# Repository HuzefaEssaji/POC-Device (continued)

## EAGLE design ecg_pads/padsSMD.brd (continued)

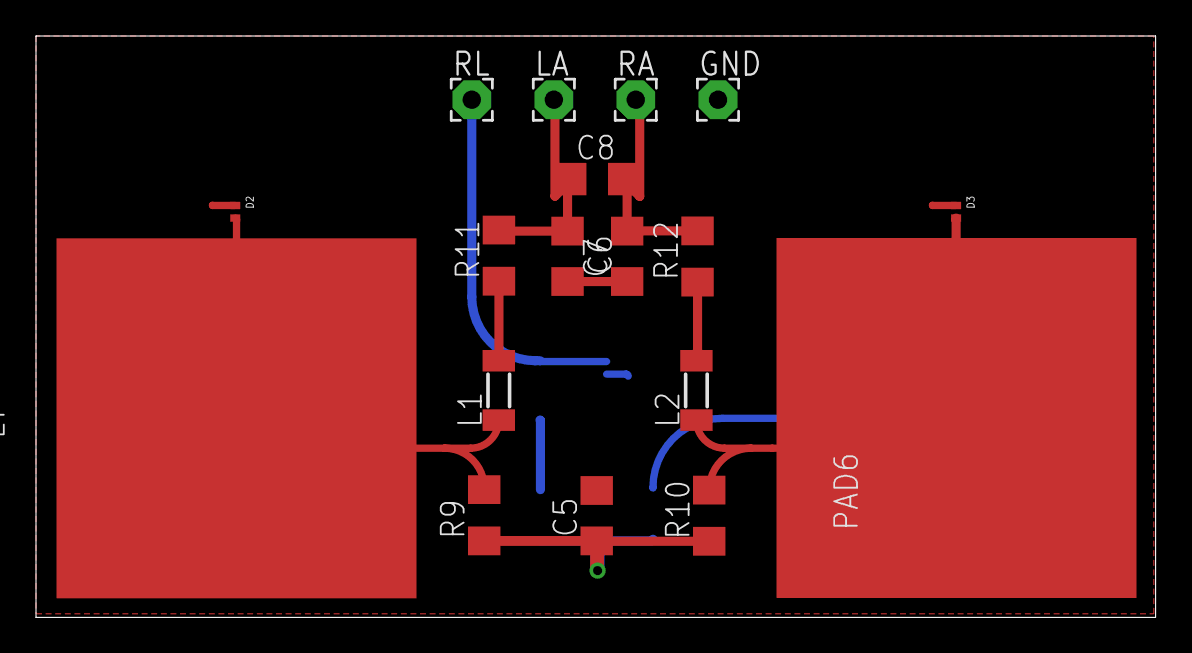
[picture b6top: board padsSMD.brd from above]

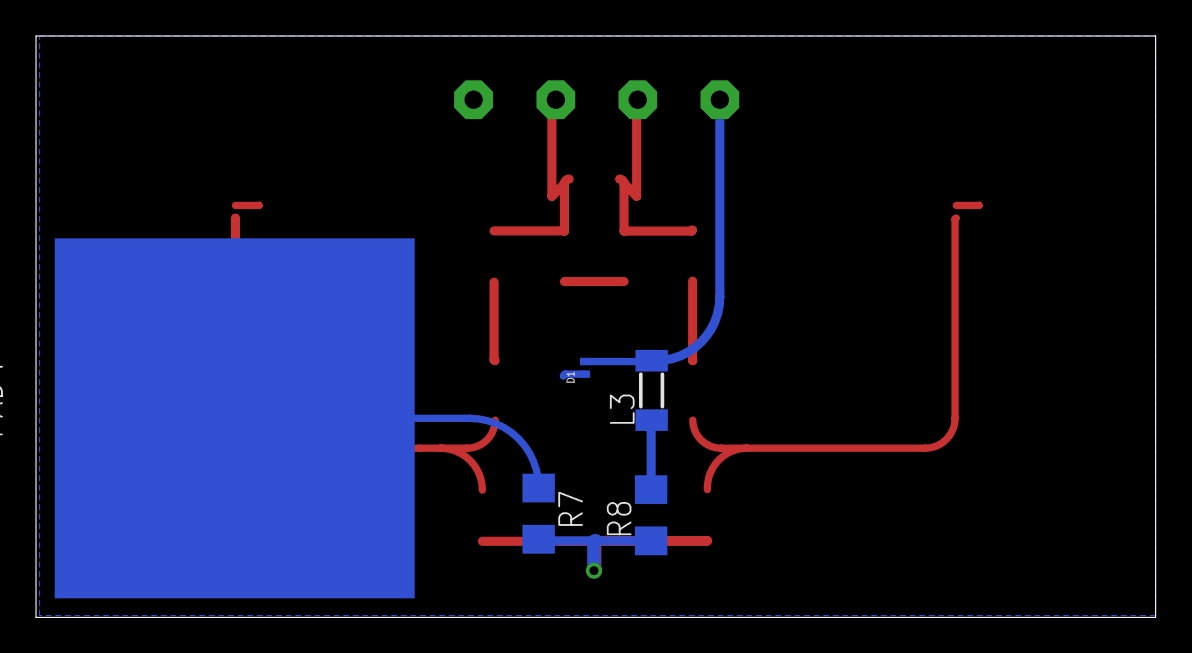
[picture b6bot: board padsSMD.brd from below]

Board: 2 copper layers, 62.2 x 32.3 mm, 23 parts (5 on the bottom side), 12 nets.

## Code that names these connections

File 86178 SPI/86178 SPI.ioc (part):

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Mcu.Name=STM32F303R(D-E)Tx
Mcu.Package=LQFP64
Mcu.UserName=STM32F303RETx
PA13.GPIOParameters=GPIO_Label
PA13.GPIO_Label=TMS
PA13.Mode=Serial_Wire
PA13.Signal=SYS_JTMS-SWDIO
PA14.GPIOParameters=GPIO_Label
PA14.GPIO_Label=TCK
PA14.Mode=Serial_Wire
PA14.Signal=SYS_JTCK-SWCLK
PA2.GPIOParameters=GPIO_Speed,GPIO_PuPd,GPIO_Label,GPIO_Mode
PA2.GPIO_Label=USART_TX
PA2.GPIO_Mode=GPIO_MODE_AF_PP
PA2.GPIO_PuPd=GPIO_NOPULL
PA2.GPIO_Speed=GPIO_SPEED_FREQ_LOW
PA2.Mode=Asynchronous
PA2.Signal=USART2_TX
PA3.GPIOParameters=GPIO_Speed,GPIO_PuPd,GPIO_Label,GPIO_Mode
PA3.GPIO_Label=USART_RX
PA3.GPIO_Mode=GPIO_MODE_AF_PP
PA3.GPIO_PuPd=GPIO_NOPULL
PA3.GPIO_Speed=GPIO_SPEED_FREQ_LOW
PA3.Mode=Asynchronous
PA3.Signal=USART2_RX
PA5.GPIOParameters=GPIO_Speed,GPIO_PuPd,GPIO_Label,GPIO_Mode
PA5.GPIO_Label=LD2 [Green Led]
PA5.GPIO_Mode=GPIO_MODE_OUTPUT_PP
PA5.GPIO_PuPd=GPIO_NOPULL
PA5.GPIO_Speed=GPIO_SPEED_FREQ_LOW
PA5.Signal=GPIO_Output
PB13.Mode=Full_Duplex_Master
PB13.Signal=SPI2_SCK
PB14.Mode=Full_Duplex_Master
PB14.Signal=SPI2_MISO
PB15.Mode=Full_Duplex_Master
PB15.Signal=SPI2_MOSI
PB3.GPIOParameters=GPIO_Label
PB3.GPIO_Label=SWO
PB3.Signal=SYS_JTDO-TRACESWO
PC13.GPIOParameters=GPIO_Label,GPIO_ModeDefaultEXTI
PC13.GPIO_Label=B1 [Blue PushButton]
PC13.GPIO_ModeDefaultEXTI=GPIO_MODE_IT_FALLING
PC13.Signal=GPXTI13
PC14-OSC32_IN.Mode=LSE-External-Oscillator
PC14-OSC32_IN.Signal=RCC_OSC32_IN
PC15-OSC32_OUT.Mode=LSE-External-Oscillator
PC15-OSC32_OUT.Signal=RCC_OSC32_OUT
PC3.Signal=GPIO_Output
PF0-OSC_IN.Mode=HSE-External-Clock-Source
PF0-OSC_IN.Signal=RCC_OSC_IN
PF1-OSC_OUT.Signal=RCC_OSC_OUT
RCC.HSE_VALUE=8000000
RCC.SYSCLKFreq_VALUE=16000000
RCC.SYSCLKSourceVirtual=RCC_SYSCLKSOURCE_PLLCLK
board=NUCLEO-F303RE
boardIOC=true

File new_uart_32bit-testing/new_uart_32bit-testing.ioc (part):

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Mcu.Name=STM32F303R(D-E)Tx
Mcu.Package=LQFP64
Mcu.UserName=STM32F303RETx
PA13.GPIOParameters=GPIO_Label
PA13.GPIO_Label=TMS
PA13.Mode=Serial_Wire
PA13.Signal=SYS_JTMS-SWDIO
PA14.GPIOParameters=GPIO_Label
PA14.GPIO_Label=TCK
PA14.Mode=Serial_Wire
PA14.Signal=SYS_JTCK-SWCLK
PA2.GPIOParameters=GPIO_Speed,GPIO_PuPd,GPIO_Label,GPIO_Mode
PA2.GPIO_Label=USART_TX
PA2.GPIO_Mode=GPIO_MODE_AF_PP
PA2.GPIO_PuPd=GPIO_NOPULL
PA2.GPIO_Speed=GPIO_SPEED_FREQ_LOW
PA2.Mode=Asynchronous
PA2.Signal=USART2_TX
PA3.GPIOParameters=GPIO_Speed,GPIO_PuPd,GPIO_Label,GPIO_Mode
PA3.GPIO_Label=USART_RX
PA3.GPIO_Mode=GPIO_MODE_AF_PP
PA3.GPIO_PuPd=GPIO_NOPULL
PA3.GPIO_Speed=GPIO_SPEED_FREQ_LOW
PA3.Mode=Asynchronous
PA3.Signal=USART2_RX
PA5.GPIOParameters=GPIO_Speed,GPIO_PuPd,GPIO_Label,GPIO_Mode
PA5.GPIO_Label=LD2 [Green Led]
PA5.GPIO_Mode=GPIO_MODE_OUTPUT_PP
PA5.GPIO_PuPd=GPIO_NOPULL
PA5.GPIO_Speed=GPIO_SPEED_FREQ_LOW
PA5.Signal=GPIO_Output
PB3.GPIOParameters=GPIO_Label
PB3.GPIO_Label=SWO
PB3.Signal=SYS_JTDO-TRACESWO
PC13.GPIOParameters=GPIO_Label,GPIO_ModeDefaultEXTI
PC13.GPIO_Label=B1 [Blue PushButton]
PC13.GPIO_ModeDefaultEXTI=GPIO_MODE_IT_FALLING
PC13.Signal=GPXTI13
PC14-OSC32_IN.Mode=LSE-External-Oscillator
PC14-OSC32_IN.Signal=RCC_OSC32_IN
PC15-OSC32_OUT.Mode=LSE-External-Oscillator
PC15-OSC32_OUT.Signal=RCC_OSC32_OUT
PC4.Mode=Asynchronous
PC4.Signal=USART1_TX
PC5.Mode=Asynchronous
PC5.Signal=USART1_RX
PF0-OSC_IN.Mode=HSE-External-Clock-Source
PF0-OSC_IN.Signal=RCC_OSC_IN
PF1-OSC_OUT.Signal=RCC_OSC_OUT
RCC.HSE_VALUE=8000000
RCC.SYSCLKFreq_VALUE=72000000
RCC.SYSCLKSourceVirtual=RCC_SYSCLKSOURCE_PLLCLK
board=NUCLEO-F303RE
boardIOC=true

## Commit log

2022-06-15 Rename ECGTemp.ino to ECGTempV6.ino
2022-06-19 tft and other comapatible libraries
2022-06-23 updated TFT libraries
2022-08-30 86178 SPI single word transaction Example
2022-09-07 Add files via upload
    Added header for max86178 PPG example
2022-09-08 Add files via upload
    86178 C Header File
2022-09-08 C Header File
2022-09-08 added SPI ppg config Functions
2022-09-11 spi functions project update until fifo reception
2022-09-12 spi_functions sample conversion
2022-09-20 uart 18 bytes reception successfull
2022-09-21 ESP32 code for transfer data via UART Bluetooth
2022-09-25 Create temp
2022-09-25 Add files via upload
    Added header files of mlx90614 temperature sensor
2022-09-25 Add files via upload
    Added Source files for mlx90614 temperature sensor
2022-09-25 Add files via upload
    ioc file added
2022-09-25 Add files via upload
    Added zipped project of mlx90614 temperature sensor
2022-10-01 Interrupt config successful
2022-10-08 esp32-reciever-script
2022-11-11 Uploads & Contributions by Parth
    Contains Project Documents
    ECG Machine Data
    ML codes and related files
2022-11-11 Add files via upload
    All word files and pdf
2022-11-11 ECG Machine Data
    xml and pdf data
2022-11-11 PDF FILES ECG
2022-11-11 ML WORK
2022-11-21 Create asa
2022-11-21 Add files via upload
    Added python script for Moving Average filters and Some file handling operations with a sample.txt file having sample PPG data tapped from Cyprus microcontroller using Logic Analyser
2022-11-25 PPG_v1.2
    Interrupt config done. Take care of proper connections especially ground and chip select. SPI divider = 8 (16mhz/8), PPG waveform plotted with window length 30 for 13000 samples. Window length has to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
2022-11-25 PPG_v1.3 with robust interrupt config
    interrupt config with enable and disable button.
2022-11-29 Create index
2022-12-02 Create ecg
2022-12-02 Add files via upload
    added the ECG project
2022-12-04 PPG_v1.4-latest-5/12/22
    flush fifo after configuring PPG or any other feature activation.
    Added powerup and shutdown functions
2022-12-04 ecg and ppg on interrupt configured properly
    just change the ppg_init to ECG_init and vice versa for the respective functionality.
2022-12-05 Add files via upload
    Added python script for PPG filtering with frequency plot
2022-12-05 Add files via upload
    Added python script for ECG filtering with frequency plot
2022-12-07 final commit
2022-12-23 Add files via upload
    Added ECG project with Bluetooth HC05 integration and controlling using mobile application
2022-12-28 Add files via upload
    Added ECG code for waveform
2023-01-17 frontend of app
2023-01-17 Revert "frontend of app"
2023-01-18 Cleared the branch
2023-01-18 Project Initialised
2023-01-18 sequelize added
2023-01-18 main
2023-01-18 Server Started
2023-01-19 typescript
2023-01-21 Data Base Finished, Graphql Queries Added
2023-01-21 updated files
2023-02-01 Queries Finished
2023-02-03 queries done
